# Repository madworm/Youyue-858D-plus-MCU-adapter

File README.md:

Youyue-858D+ MCU-adapter:
=========================

LAYOUT FILES: ATmega168/328 adapter board for the Youyue 858D+.  

The purpose if this little board is to add an ISP header and a convenient way of adding
more stuff via some TH solder pads.

The old MCU (ATmega8) + socket are removed and replaced with a new DIP28 socket (machined pins).
These same machined pins go into the bigger holes of the adapter board and form a
low-profile socket for the new MCU (ATmega168). The adapter board then plugs into
the socket on the main circuit board.

Firmware [repository](https://github.com/madworm/Youyue-858D-plus).

---

Safety information / disclaimer:
================================
                                                                                                                                                             
Making any modifications to this device may cause you irreversible physical harm or worse.                                                                   
You do this at your own risk.                                                                                                                                
                                                                                                                                                             
There is a significant risk of lethal electrical shock, so if you still insist of doing so, make sure to                                                     
ALWAYS UNPLUG THE MAINS CABLE before dismantling the device. Check repeatedly.                                                                               
                                                                                                                                                             
If you have an isolation transformer - do use it.

---

Before having PC-boards made, please make sure you know about your manufacturer's peculiarities!
Especially drill-sizes and their tolerances may vary too much and give you trouble.

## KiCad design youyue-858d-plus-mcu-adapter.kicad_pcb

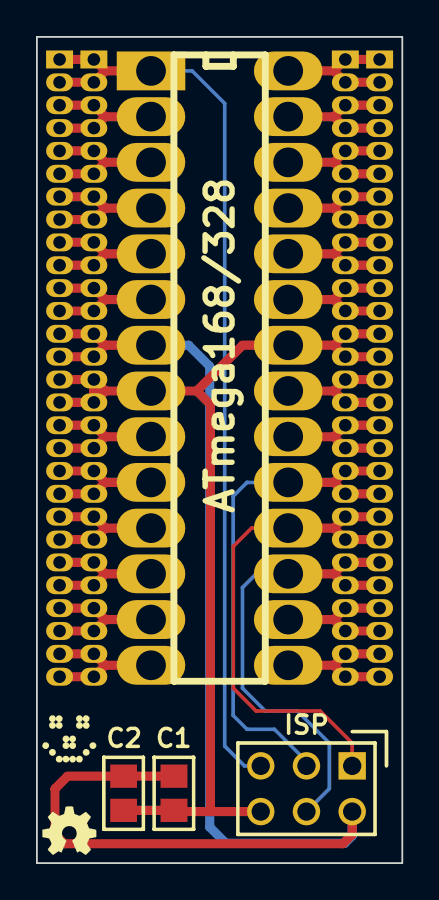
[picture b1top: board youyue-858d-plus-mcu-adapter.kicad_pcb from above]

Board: 2 copper layers, 20.3 x 45.9 mm, 14 parts (0 on the bottom side), 27 nets.

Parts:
C1, C2: 10µF; MADW__C0805
G1: OSHW-logo_silkscreen_3mm
G2: LED_smile_silkscreen_3mm
JP1: ISP; pin_array_3x2
P1: MADW__DIL28; DIP-28__300_ELL
P2, P3, P4, P5, P6, P7, P8, P9: CONN_14; MADW__SIL-14-1.27mm

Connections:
/GND: C1.2, C2.2, JP1.6, P1.8, P1.22, P4.1, P4.2, P5.1, P5.2, P6.13, P6.14, P7.13, P7.14
/MISO: JP1.1, P1.18, P8.7, P8.8, P9.7, P9.8
/MOSI: JP1.4, P1.17, P8.9, P8.10, P9.9, P9.10
/RST: JP1.5, P1.1, P2.1, P2.2, P3.1, P3.2
/SCK: JP1.3, P1.19, P8.5, P8.6, P9.5, P9.6
/VCC: C1.1, C2.1, JP1.2, P1.7, P2.13, P2.14, P3.13, P3.14
unnamed: P1.2, P2.3, P2.4, P3.3, P3.4
unnamed: P1.3, P2.5, P2.6, P3.5, P3.6
unnamed: P1.4, P2.7, P2.8, P3.7, P3.8
unnamed: P1.5, P2.9, P2.10, P3.9, P3.10
unnamed: P1.6, P2.11, P2.12, P3.11, P3.12
unnamed: P1.9, P4.3, P4.4, P5.3, P5.4
unnamed: P1.10, P4.5, P4.6, P5.5, P5.6
unnamed: P1.11, P4.7, P4.8, P5.7, P5.8
unnamed: P1.12, P4.9, P4.10, P5.9, P5.10
unnamed: P1.13, P4.11, P4.12, P5.11, P5.12
unnamed: P1.14, P4.13, P4.14, P5.13, P5.14
unnamed: P1.15, P8.13, P8.14, P9.13, P9.14
unnamed: P1.16, P8.11, P8.12, P9.11, P9.12
unnamed: P1.20, P8.3, P8.4, P9.3, P9.4
unnamed: P1.21, P8.1, P8.2, P9.1, P9.2
unnamed: P1.23, P6.11, P6.12, P7.11, P7.12
unnamed: P1.24, P6.9, P6.10, P7.9, P7.10
unnamed: P1.25, P6.7, P6.8, P7.7, P7.8
unnamed: P1.26, P6.5, P6.6, P7.5, P7.6
unnamed: P1.27, P6.3, P6.4, P7.3, P7.4
unnamed: P1.28, P6.1, P6.2, P7.1, P7.2

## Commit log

2013-12-06 Added some docs.
2013-12-06 Updated 'README.md'.
2013-12-06 Fixed a soldermask blunder.
2013-12-08 Added safety warning to 'README.md'.
2014-01-05 Added image of finished board to 'Docs' folder.
2014-02-12 Added a couple of illustrative images to 'Docs' folder.
2015-10-09 Updated a script.
2016-01-11 Renamed schematic pdf.
2016-01-11 Updated 'Docs/readme.txt'.
